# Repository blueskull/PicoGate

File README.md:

# PicoGate
A tiny FPGA core module featuring GW1NZ-LV1.

This module contains a Gowin GW1NZ-LV1 FPGA in 6mm\*6mm QFN48 package, a WCH CH552 USB MCU in 3mm\*3mm QFN16 package, and a Dialog Semiconductor (formerly SiLego) SLG46580 PMIC in 2mm\*3mm QFN20 package. The FPGA has 23 IOs brought out, referenced at a programmable IO voltage (by default, 1.8V and 3.3V switchable), with an additional of 2 fixed 3.3V IOs and 3 high voltage (5V) IOs, expanded through SLG46580. The MCU provides USB-JTAG and USB-SPI bridging, clock generation and supply voltage supervision, while the PMIC provides 1.2V, 3.3V and programmable VIO as well as 5V logic level shifting.

The entire module is packaged in a space saving 9.0mm\*10.0mm BGA package with 23+2+3 digital IO pads, 1.2V/3.3V/VIO regulator output pads, 5V and USB pads and ample of ground pads. As of early-2022, the budgetary 1kpcs BOM cost is around $2.5, making it ideal for adding simple custom logics to any existing designs.

The hardware and GreenPak firmware designs are licensed under the unlicense license, meaning you can basically do whatever you'd like with it, but the author kindly asks you to do good things and give more then you take. The MCU firmware is stored in my ch552-jtag repository and is licensed accordingly.

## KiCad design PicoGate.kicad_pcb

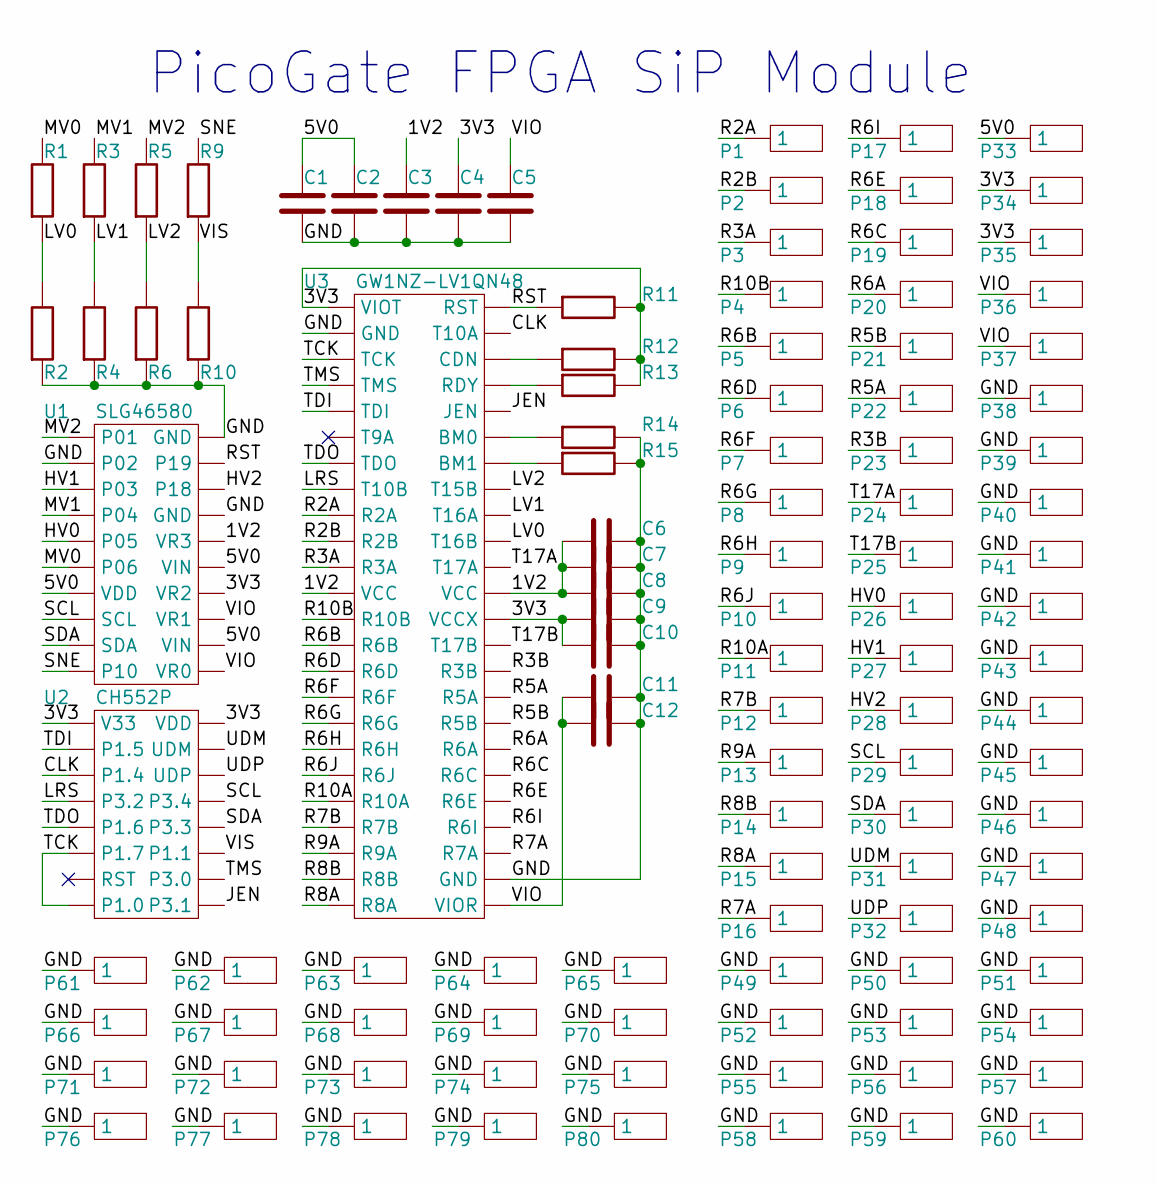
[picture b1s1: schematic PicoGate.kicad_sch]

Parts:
C1, C2, C3, C4, C5, C6, C7, C8, C9, C10, C11, C12: Capacitor; 0201
P1, P2, P3, P4, P5, P6, P7, P8, P9, P10, P11, P12, P13, P14, P15, P16, P17, P18, P19, P20, P21, P22, P23, P24, P25, P26, P27, P28, P29, P30, P31, P32, P33, P34, P35, P36, P37, P38, P39, P40, P41, P42, P43, P44, P45, P46, P47, P48, P49, P50, P51, P52, P53, P54, P55, P56, P57, P58, P59, P60, P61, P62, P63, P64, P65, P66, P67, P68, P69, P70, P71, P72, P73, P74, P75, P76, P77, P78, P79, P80: CONN1X1; PAD1_0.35_0.35_R
R1, R2, R3, R4, R5, R6, R9, R10, R11, R12, R13, R14, R15: Resistor; 0201
U1: SLG46580; QFN20_3.0_2.0_0.4_US
U2: CH552P; QFN16_3.0_3.0_0.5_US
U3: GW1NZ-LV1QN48; QFN48_6.0_6.0_0.4_US

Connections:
/1V2: C3.1, C6.2, C7.2, C8.2, U1.16 (VR3), U3.12 (VCC), U3.37 (VCC)
/3V3: C4.1, C9.2, C10.2, P34.1, P35.1, R11.1, R12.1, R13.1, U1.14 (VR2), U2.1 (V33), U2.16 (VDD), U3.1 (VIOT), U3.36 (VCCX)
/5V0: C1.1, C2.1, P33.1, U1.7 (VDD), U1.12 (VIN), U1.15 (VIN)
/CLK: U2.3 (P1.4), U3.47 (T10A)
/GND: C1.2, C2.2, C3.2, C4.2, C5.2, C6.1, C7.1, C8.1, C9.1, C10.1, C11.1, C12.1, P38.1, P39.1, P40.1, P41.1, P42.1, P43.1, P44.1, P45.1, P46.1, P47.1, P48.1, P49.1, P50.1, P51.1, P52.1, P53.1, P54.1, P55.1, P56.1, P57.1, P58.1, P59.1, P60.1, P61.1, P62.1, P63.1, P64.1, P65.1, P66.1, P67.1, P68.1, P69.1, P70.1, P71.1, P72.1, P73.1, P74.1, P75.1, P76.1, P77.1, P78.1, P79.1, P80.1, R2.2, R4.2, R6.2, R10.2, R14.1, R15.1, U1.2, U1.17 (GND), U1.20 (GND), U3.2 (GND), U3.26 (GND)
/HV0: P26.1, U1.5
/HV1: P27.1, U1.3
/HV2: P28.1, U1.18
/JEN: U2.9 (P3.1), U3.44 (JEN)
/LRS: U2.4 (P3.2), U3.8 (T10B)
/LV0: R1.2, R2.1, U3.39 (T16B)
/LV1: R3.2, R4.1, U3.40 (T16A)
/LV2: R5.2, R6.1, U3.41 (T15B)
/MV0: R1.1, U1.6
/MV1: R3.1, U1.4
/MV2: R5.1, U1.1
/R2A: P1.1, U3.9 (R2A)
/R2B: P2.1, U3.10 (R2B)
/R3A: P3.1, U3.11 (R3A)
/R3B: P23.1, U3.34 (R3B)
/R5A: P22.1, U3.33 (R5A)
/R5B: P21.1, U3.32 (R5B)
/R6A: P20.1, U3.31 (R6A)
/R6B: P5.1, U3.14 (R6B)
/R6C: P19.1, U3.30 (R6C)
/R6D: P6.1, U3.15 (R6D)
/R6E: P18.1, U3.29 (R6E)
/R6F: P7.1, U3.16 (R6F)
/R6G: P8.1, U3.17 (R6G)
/R6H: P9.1, U3.18 (R6H)
/R6I: P17.1, U3.28 (R6I)
/R6J: P10.1, U3.19 (R6J)
/R7A: P16.1, U3.27 (R7A)
/R7B: P12.1, U3.21 (R7B)
/R8A: P15.1, U3.24 (R8A)
/R8B: P14.1, U3.23 (R8B)
/R9A: P13.1, U3.22 (R9A)
/R10A: P11.1, U3.20 (R10A)
/R10B: P4.1, U3.13 (R10B)
/RST: R11.2, U1.19, U3.48 (RST)
/SCL: P29.1, U1.8 (SCL), U2.13 (P3.4)
/SDA: P30.1, U1.9 (SDA), U2.12 (P3.3)
/SNE: R9.1, U1.10
/T17A: P24.1, U3.38 (T17A)
/T17B: P25.1, U3.35 (T17B)
/TCK: U2.6 (P1.7), U2.8 (P1.0), U3.3 (TCK)
/TDI: U2.2 (P1.5), U3.5 (TDI)
/TDO: U2.5 (P1.6), U3.7 (TDO)
/TMS: U2.10 (P3.0), U3.4 (TMS)
/UDM: P31.1, U2.15 (UDM)
/UDP: P32.1, U2.14 (UDP)
/VIO: C5.1, C11.2, C12.2, P36.1, P37.1, U1.11 (VR0), U1.13 (VR1), U3.25 (VIOR)
/VIS: R9.2, R10.1, U2.11 (P1.1)
unnamed: R12.2, U3.46 (CDN)
unnamed: R13.2, U3.45 (RDY)
unnamed: R14.2, U3.43 (BM0)
unnamed: R15.2, U3.42 (BM1)

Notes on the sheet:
PicoGate FPGA SiP Module

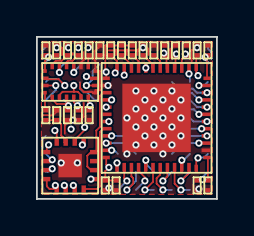
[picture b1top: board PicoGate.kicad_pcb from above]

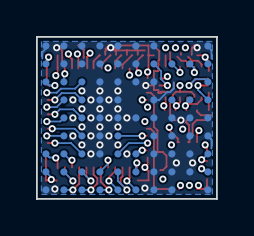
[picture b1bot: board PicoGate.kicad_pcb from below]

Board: 4 copper layers, 10.0 x 9.0 mm, 108 parts (80 on the bottom side), 57 nets.

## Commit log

2022-01-07 Update to rev 4
    Changed package from LGA to BGA, added one programmable voltage IO, removed one fixed voltage IO, added one 5V IO, removed capability of changing 5V IO direction on-the-go by FPGA, shrunk board size.
